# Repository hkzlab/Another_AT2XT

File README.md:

# Another AT2XT Adapter

## Introduction

This is nothing more than another PCB for the AT2XT project you can find [HERE](https://www.vcfed.org/forum/forum/vcwiki/vcwiki-aa/26861-at2xt-keyboard-converter?26426-AT2XT-keyboard-converter=).

I needed something slightly smaller than what provided for the original project, and that did not need as many connector cables. So I've designed this to cater to my needs.

### Disclaimer

I take NO responsibility for what happens if you decide to build and use this card. Your computer might crash, catch fire or be destroyed in other nasty ways.
You're encourauged to take what you deem fit from this, and use it in your projects!

### Pinout of XT connector

```text
1 - KB CLOCK
2 - KB DATA
3 - NC
4 - GND
5 - +5v
```

## Bill of Materials

```text
- J1: Wire it to a cable ending in a 5 pin DIN according to the pinout above
- J2: 6-pin mini-din female. Mouser 571-5749180-1
- JP1: 2 pin male header, 2.54mm spacing
- D1: 1N4148
- U1: PIC12F629, DIP8
- RN1: 3x10k bussed resistor, 4 pin. Mouser 652-4604X-1LF-10K
- C1: 100nF ceramic capacitor, 5mm spacing
- C2: 10uF ceramic capacitor, 5mm spacing
- F1: A wire if you're feeling adventurous, otherwise a polyfuse with 5.08mm spacing, e.g. Mouser 576-16R110BPR
```

Remember to flash the PIC!!! You can find the HEX at the link in the introduction section.

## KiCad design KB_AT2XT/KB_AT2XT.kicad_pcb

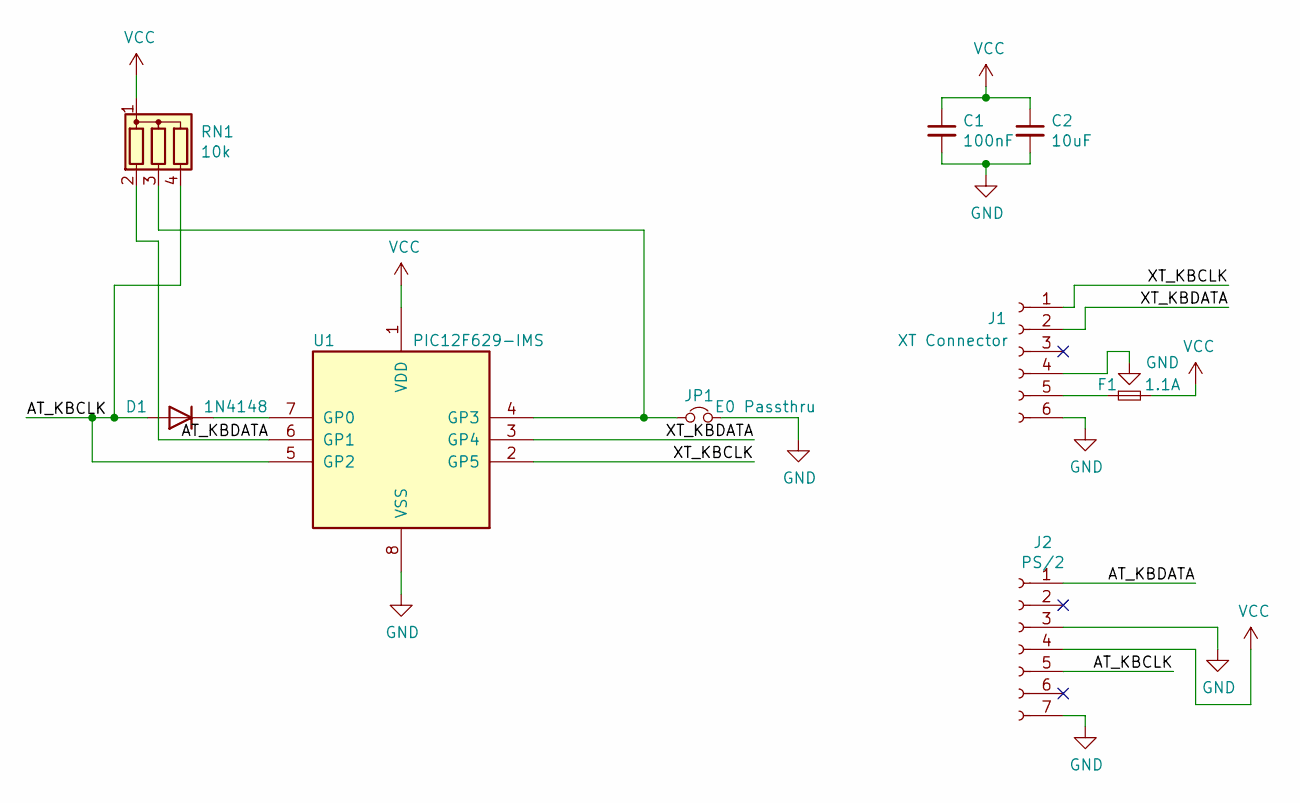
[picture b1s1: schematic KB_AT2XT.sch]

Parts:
C1: 100nF; C_Disc_D6.0mm_W2.5mm_P5.00mm
C2: 10uF; C_Disc_D6.0mm_W2.5mm_P5.00mm
D1: 1N4148; D_DO-35_SOD27_P7.62mm_Horizontal
F1: 1.1A; Fuse_Littelfuse_395Series
J1: XT Connector; PinHeader_1x06_P2.54mm_Vertical
J2: PS/2; Connector_Mini-DIN_Female_6Pin_2rows
JP1: E0 Passthru; PinSocket_1x02_P2.54mm_Vertical
RN1: 10k; R_Array_SIP4
U1: PIC12F629-IMS; DIP-8_W7.62mm_LongPads

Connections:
/AT_KBCLK: D1.2 (A), J2.5, RN1.4 (R3), U1.5 (GP2)
/AT_KBDATA: J2.1, RN1.2 (R1), U1.6 (GP1)
/XT_KBCLK: J1.1, U1.2 (GP5)
/XT_KBDATA: J1.2, U1.3 (GP4)
GND: C1.2, C2.2, J1.4, J1.6, J2.3, J2.7, JP1.2, U1.8 (VSS)
unnamed: D1.1 (K), U1.7 (GP0)
unnamed: F1.1, J1.5
unnamed: JP1.1, RN1.3 (R2), U1.4 (GP3)
VCC: C1.1, C2.1, F1.2, J2.4, RN1.1 (common), U1.1 (VDD)

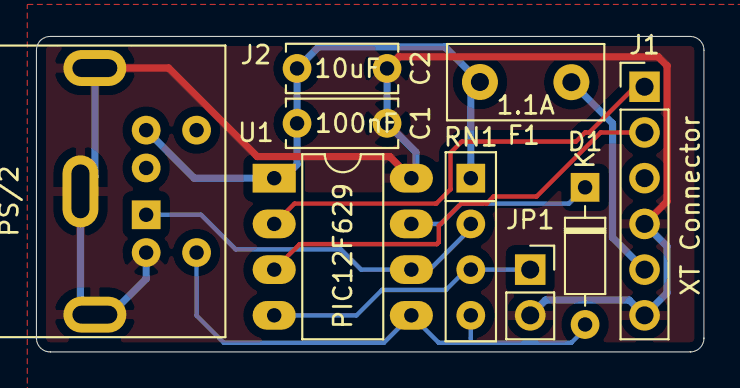
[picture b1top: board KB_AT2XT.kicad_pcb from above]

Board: 2 copper layers, 37.1 x 17.5 mm, 9 parts (0 on the bottom side), 9 nets.

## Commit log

2021-05-28 Add gitignore
2021-05-28 Add gerbers
2021-06-16 Cleaned up project
2021-06-17 Add README and pics
2021-06-17 Add reminder about flashing the PIC
2021-06-17 Better warning
